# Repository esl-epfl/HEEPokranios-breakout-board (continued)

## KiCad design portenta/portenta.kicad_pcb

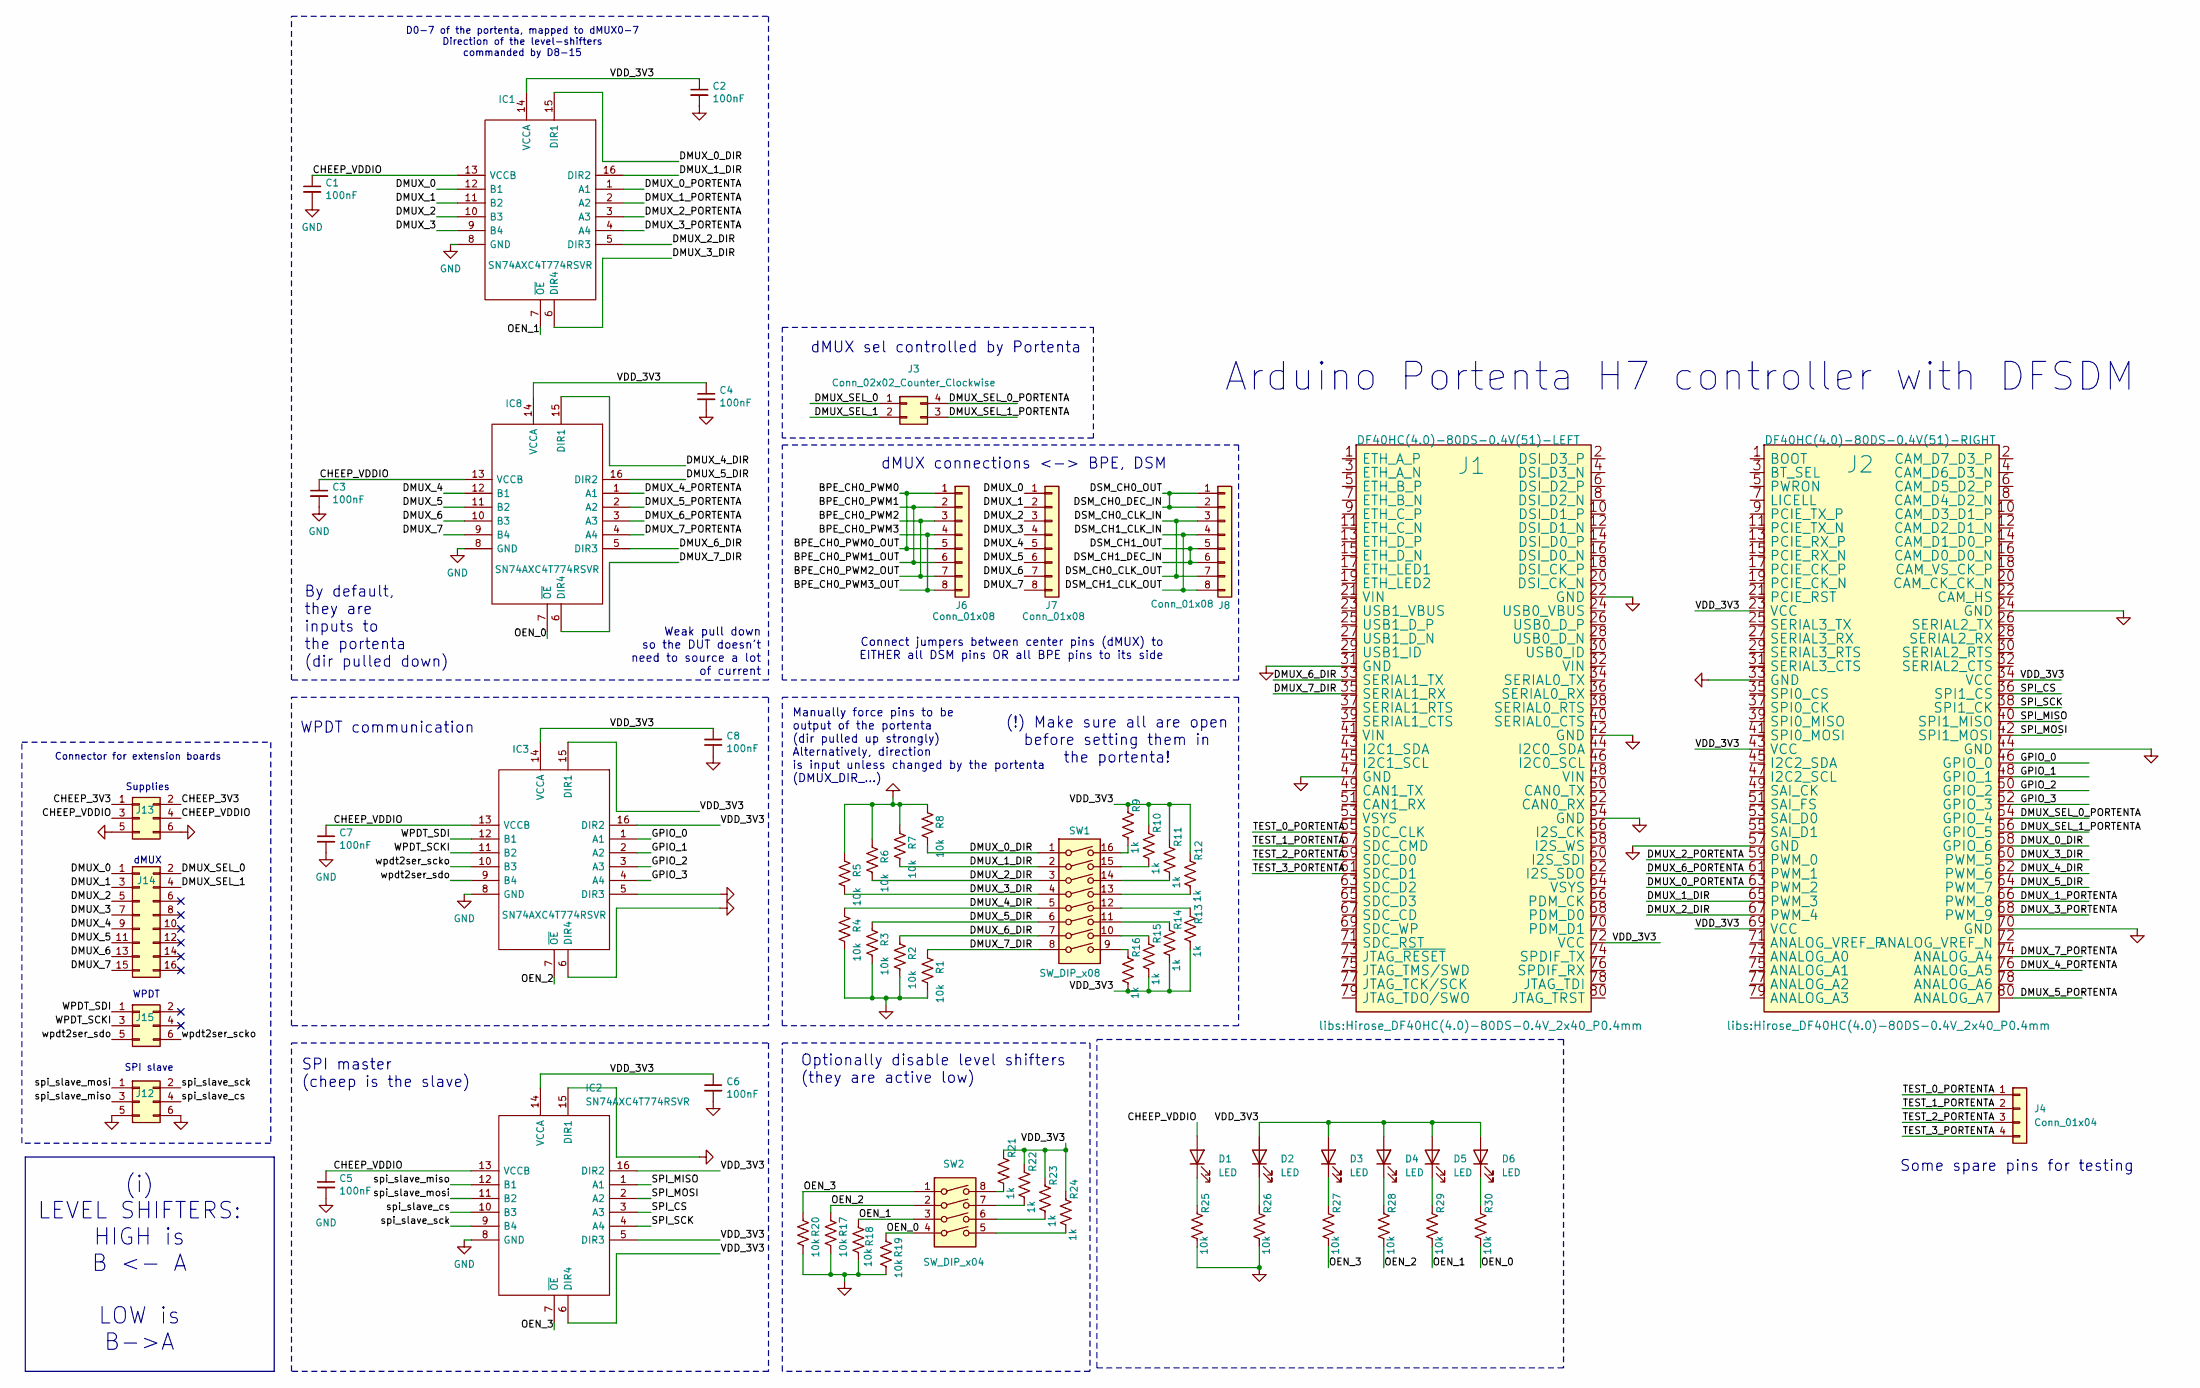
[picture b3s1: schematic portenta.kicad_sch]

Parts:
C1, C2, C3, C4, C5, C6, C7, C8: 100nF; C_0603_1608Metric; Mouser Part Number 80-C0805C104Z3V; Digikey Part Number 399-9158-1-ND
D1, D2, D3, D4, D5, D6: LED; LED_0603_1608Metric
IC1, IC2, IC3, IC8: SN74AXC4T774RSVR; TI-UQFN-16; Manufacturer_Part_Number SN74AXC4T774RSVR; Mouser Part Number 595-SN74AXC4T774RSVR
J1: DF40HC(4.0)-80DS-0.4V(51)-LEFT; Hirose_DF40HC(4.0)-80DS-0.4V_2x40_P0.4mm
J2: DF40HC(4.0)-80DS-0.4V(51)-RIGHT; Hirose_DF40HC(4.0)-80DS-0.4V_2x40_P0.4mm
J3: Conn_02x02_Counter_Clockwise; PinHeader_2x02_P2.54mm_Vertical
J4: Conn_01x04; PinHeader_1x04_P2.54mm_Vertical
J6, J7, J8: Conn_01x08; PinHeader_1x08_P2.54mm_Vertical
J12, J13, J15: Conn_02x03_Odd_Even; PinHeader_2x03_P2.54mm_Horizontal
J14: Conn_02x08_Odd_Even; PinHeader_2x08_P2.54mm_Horizontal
R1, R2, R3, R4, R5, R6, R7, R8, R17, R18, R19, R20, R25, R26, R27, R28, R29, R30: 10k; R_0603_1608Metric
R9, R10, R11, R12, R13, R14, R15, R16, R21, R22, R23, R24: 1k; R_0603_1608Metric
SW1: SW_DIP_x08; SW_DIP_SPSTx08_Slide_6.7x21.88mm_W8.61mm_P2.54mm_LowProfile
SW2: SW_DIP_x04; SW_DIP_SPSTx04_Slide_6.7x11.72mm_W8.61mm_P2.54mm_LowProfile

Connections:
/BPE_CH0_PWM0: J6.1, J6.5
/BPE_CH0_PWM1: J6.2, J6.6
/BPE_CH0_PWM2: J6.3, J6.7
/BPE_CH0_PWM3: J6.4, J6.8
/CHEEP_3V3: J13.1, J13.2
/CHEEP_VDDIO: C1.1, C3.1, C5.1, C7.1, D1.2 (A), IC1.13 (VCCB), IC2.13 (VCCB), IC3.13 (VCCB), IC8.13 (VCCB), J13.3, J13.4
/DMUX_0: IC1.12 (B1), J7.1, J14.1
/DMUX_0_DIR: IC1.15 (DIR1), J2.58 (GPIO_6), R8.2, SW1.1
/DMUX_0_PORTENTA: IC1.1 (A1), J2.63 (PWM_2)
/DMUX_1: IC1.11 (B2), J7.2, J14.3
/DMUX_1_DIR: IC1.16 (DIR2), J2.65 (PWM_3), R7.2, SW1.2
/DMUX_1_PORTENTA: IC1.2 (A2), J2.66 (PWM_8)
/DMUX_2: IC1.10 (B3), J7.3, J14.5
/DMUX_2_DIR: IC1.5 (DIR3), J2.67 (PWM_4), R6.2, SW1.3
/DMUX_2_PORTENTA: IC1.3 (A3), J2.59 (PWM_0)
/DMUX_3: IC1.9 (B4), J7.4, J14.7
/DMUX_3_DIR: IC1.6 (DIR4), J2.60 (PWM_5), R5.2, SW1.4
/DMUX_3_PORTENTA: IC1.4 (A4), J2.68 (PWM_9)
/DMUX_4: IC8.12 (B1), J7.5, J14.9
/DMUX_4_DIR: IC8.15 (DIR1), J2.62 (PWM_6), R4.1, SW1.5
/DMUX_4_PORTENTA: IC8.1 (A1), J2.76 (ANALOG_A5)
/DMUX_5: IC8.11 (B2), J7.6, J14.11
/DMUX_5_DIR: IC8.16 (DIR2), J2.64 (PWM_7), R3.1, SW1.6
/DMUX_5_PORTENTA: IC8.2 (A2), J2.80 (ANALOG_A7)
/DMUX_6: IC8.10 (B3), J7.7, J14.13
/DMUX_6_DIR: IC8.5 (DIR3), J1.33 (SERIAL1_TX), R2.1, SW1.7
/DMUX_6_PORTENTA: IC8.3 (A3), J2.61 (PWM_1)
/DMUX_7: IC8.9 (B4), J7.8, J14.15
/DMUX_7_DIR: IC8.6 (DIR4), J1.35 (SERIAL1_RX), R1.1, SW1.8
/DMUX_7_PORTENTA: IC8.4 (A4), J2.74 (ANALOG_A4)
/DMUX_SEL_0: J3.1, J14.2
/DMUX_SEL_0_PORTENTA: J2.54 (GPIO_4), J3.4
/DMUX_SEL_1: J3.2, J14.4
/DMUX_SEL_1_PORTENTA: J2.56 (GPIO_5), J3.3
/DSM_CH0_CLK_IN: J8.3, J8.7
/DSM_CH0_DEC_IN: J8.1, J8.2
/DSM_CH1_CLK_IN: J8.4, J8.8
/DSM_CH1_DEC_IN: J8.5, J8.6
/GPIO_0: IC3.1 (A1), J2.46 (GPIO_0)
/GPIO_1: IC3.2 (A2), J2.48 (GPIO_1)
/GPIO_2: IC3.3 (A3), J2.50 (GPIO_2)
/GPIO_3: IC3.4 (A4), J2.52 (GPIO_3)
/OEN_0: IC8.7 (~OE), R19.1, R30.2, SW2.4
/OEN_1: IC1.7 (~OE), R18.1, R29.2, SW2.3
/OEN_2: IC3.7 (~OE), R17.1, R28.2, SW2.2
/OEN_3: IC2.7 (~OE), R20.1, R27.2, SW2.1
/SPI_CS: IC2.3 (A3), J2.36 (SPI1_CS)
/SPI_MISO: IC2.1 (A1), J2.40 (SPI1_MISO)
/SPI_MOSI: IC2.2 (A2), J2.42 (SPI1_MOSI)
/SPI_SCK: IC2.4 (A4), J2.38 (SPI1_CK)
/TEST_0_PORTENTA: J1.55 (SDC_CLK), J4.1
/TEST_1_PORTENTA: J1.57 (SDC_CMD), J4.2
/TEST_2_PORTENTA: J1.59 (SDC_D0), J4.3
/TEST_3_PORTENTA: J1.61 (SDC_D1), J4.4
/VDD_3V3: C2.1, C4.1, C6.1, C8.1, D2.2 (A), D3.2 (A), D4.2 (A), D5.2 (A), D6.2 (A), IC1.14 (VCCA), IC2.5 (DIR3), IC2.6 (DIR4), IC2.14 (VCCA), IC2.16 (DIR2), IC3.14 (VCCA), IC3.15 (DIR1), IC3.16 (DIR2), IC8.14 (VCCA), J1.72 (VCC), J2.23 (VCC), J2.34 (VCC), J2.43 (VCC), J2.69 (VCC), R9.1, R10.1, R11.1, R12.1, R13.2, R14.2, R15.2, R16.2, R21.1, R22.1, R23.1, R24.1
/WPDT_SCKI: IC3.11 (B2), J15.3
/WPDT_SDI: IC3.12 (B1), J15.1
/spi_slave_cs: IC2.10 (B3), J12.4
/spi_slave_miso: IC2.12 (B1), J12.3
/spi_slave_mosi: IC2.11 (B2), J12.1
/spi_slave_sck: IC2.9 (B4), J12.2
/wpdt2ser_scko: IC3.10 (B3), J15.6
/wpdt2ser_sdo: IC3.9 (B4), J15.5
GND: C1.2, C2.2, C3.2, C4.2, C5.2, C6.2, C7.2, C8.2, IC1.8 (GND), IC2.8 (GND), IC2.15 (DIR1), IC3.5 (DIR3), IC3.6 (DIR4), IC3.8 (GND), IC8.8 (GND), J1.22 (GND), J1.31 (GND), J1.42 (GND), J1.47 (GND), J1.54 (GND), J2.24 (GND), J2.33 (GND), J2.44 (GND), J2.57 (GND), J2.70 (GND), J12.5, J12.6, J13.5, J13.6, R1.2, R2.2, R3.2, R4.2, R5.1, R6.1, R7.1, R8.1, R17.2, R18.2, R19.2, R20.2, R25.2, R26.2
unnamed: D1.1 (K), R25.1
unnamed: D2.1 (K), R26.1
unnamed: D3.1 (K), R27.1
unnamed: D4.1 (K), R28.1
unnamed: D5.1 (K), R29.1
unnamed: D6.1 (K), R30.1
unnamed: R9.2, SW1.16
unnamed: R10.2, SW1.15
unnamed: R11.2, SW1.14
unnamed: R12.2, SW1.13
unnamed: R13.1, SW1.12
unnamed: R14.1, SW1.11
unnamed: R15.1, SW1.10
unnamed: R16.1, SW1.9
unnamed: R21.2, SW2.8
unnamed: R22.2, SW2.7
unnamed: R23.2, SW2.6
unnamed: R24.2, SW2.5

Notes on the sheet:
Some spare pins for testing
Connect jumpers between center pins (dMUX) to EITHER all DSM pins OR all BPE pins to its side
(i) LEVEL SHIFTERS: HIGH is B <- A LOW is B->A
Weak pull down so the DUT doesn't need to source a lot of current
Arduino Portenta H7 controller with DFSDM
Optionally disable level shifters (they are active low)
WPDT
SPI slave
Manually force pins to be output of the portenta (dir pulled up strongly) Alternatively, direction is input unless changed by the portenta (DMUX_DIR_...)
dMUX connections <-> BPE, DSM
WPDT communication
dMUX
SPI master (cheep is the slave)
Supplies
D0-7 of the portenta, mapped to dMUX0-7 Direction of the level-shifters commanded by D8-15
Connector for extension boards
By default, they are inputs to the portenta (dir pulled down)
(!) Make sure all are open before setting them in the portenta!
dMUX sel controlled by Portenta

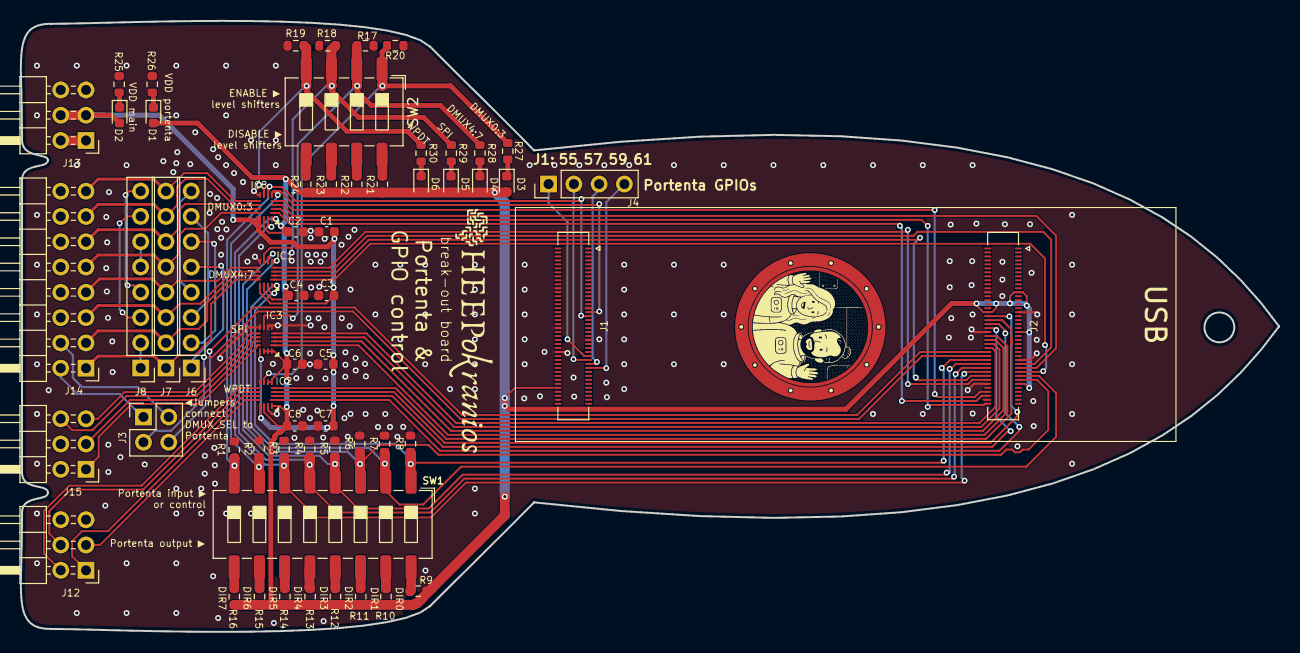
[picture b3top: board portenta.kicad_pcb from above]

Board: 2 copper layers, 126.4 x 61.4 mm, 61 parts (0 on the bottom side), 82 nets.

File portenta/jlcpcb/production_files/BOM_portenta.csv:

Comment,Designator,Footprint,LCSC,Qty
100n,"C1,C2,C3,C4,C5,C6,C7,C8",C_0603_1608Metric,C30926,8
LED,"D1,D2,D3,D4,D5,D6",LED_0603_1608Metric,C84263,6
SN74AXC4T774RSVR,"IC1,IC2,IC3,IC8",TI-UQFN-16,C1849454,4
DF40HC(4.0)-80DS-0.4V(51),"J1,J2",Hirose_DF40HC(4.0)-80DS-0.4V_2x40_P0.4mm,C5254351,2
Conn_02x02_Counter_Clockwise,J3,PinHeader_2x02_P2.54mm_Vertical,C66690,1
Conn_01x04,J4,PinHeader_1x04_P2.54mm_Vertical,C52016392,1
Conn_01x08,"J6,J7,J8",PinHeader_1x08_P2.54mm_Vertical,C32713274,3
Conn_02x03_Odd_Even,"J12,J13,J15",PinHeader_2x03_P2.54mm_Horizontal,C41417351,3
Conn_02x08_Odd_Even,J14,PinHeader_2x08_P2.54mm_Horizontal,C41417356,1
10k,"R1,R2,R3,R4,R5,R6,R7,R8,R17,R18,R19,R20,R25,R26,R27,R28,R29,R30",R_0603_1608Metric,C2930027,18
1k,"R9,R10,R11,R12,R13,R14,R15,R16,R21,R22,R23,R24",R_0603_1608Metric,C110776,12
SW_DIP_x08,SW1,SW_DIP_SPSTx08_Slide_6.7x21.88mm_W8.61mm_P2.54mm_LowProfile,C5439767,1
SW_DIP_x04,SW2,SW_DIP_SPSTx04_Slide_6.7x11.72mm_W8.61mm_P2.54mm_LowProfile,C5439763,1

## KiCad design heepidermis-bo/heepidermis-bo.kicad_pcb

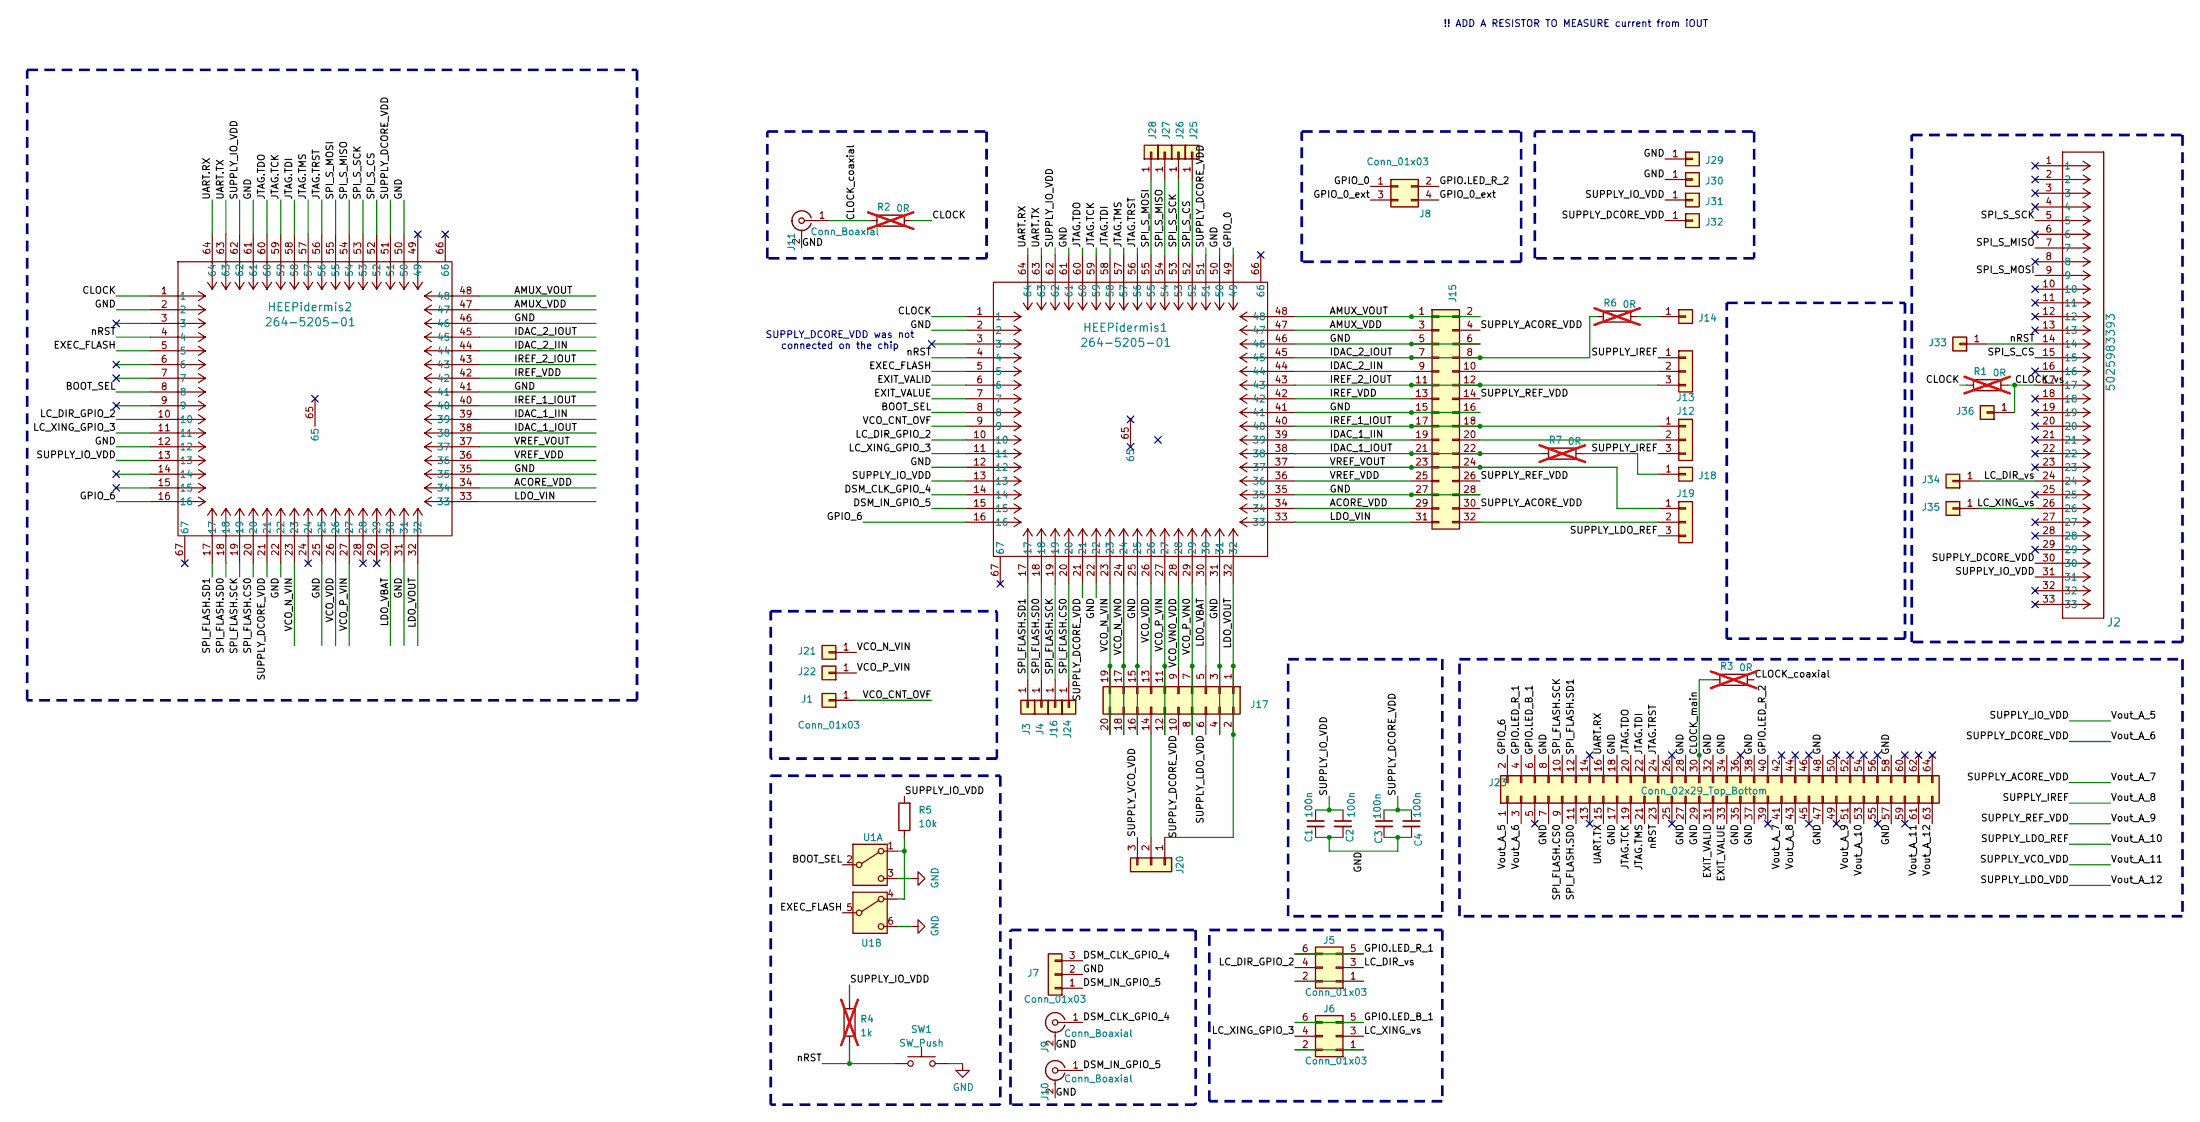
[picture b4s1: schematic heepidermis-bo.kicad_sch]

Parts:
C1, C2, C3, C4: 100n; C_0603_1608Metric; Mouser Part Number 80-C0805C104Z3V; Digikey Part Number 399-9158-1-ND
HEEPidermis1: 264-5205-01; CONN_5205_3MM
HEEPidermis2: 264-5205-01; QFN-64-1EP_9x9mm_P0.5mm_EP3.4x3.4mm
J1, J14, J18, J21, J22: Conn_01x03; PinHeader_1x01_P1.27mm_Vertical
J2: 5025983393; CONN_502598-3393_MOL
J3, J4, J16, J24, J25, J26, J27, J28, J29, J30, J31, J32, J33, J34, J35, J36: Conn_01x03; TestPoint_THTPad_1.0x1.0mm_Drill0.5mm
J5, J6: Conn_01x03; PinHeader_2x03_P1.27mm_Vertical
J7, J12, J13, J19, J20: Conn_01x03; PinHeader_1x03_P2.54mm_Vertical
J8: Conn_01x03; PinHeader_2x02_P1.27mm_Vertical
J9, J10, J11: Conn_Boaxial; SMA_Amphenol_901-144_Vertical
J15: Conn_02x16_Odd_Even; PinHeader_02x16_P2.54mm_Vertical
J17: Conn_02x10_Odd_Even; PinHeader_2x10_P2.54mm_Vertical
J23: Conn_02x29_Top_Bottom; PinHeader_2x32_P2.54mm_Vertical
R1, R2, R3: 0R; R0402; not fitted
R4: 1k; R_0603_1608Metric; LCSC C21190; not fitted
R5: 10k; R_0603_1608Metric; LCSC C21190
R6, R7: 0R; R_0402_1005Metric; not fitted
SW1: SW_Push; SW_Push_1P1T_NO_CK_KMR2
U1: SPDT-2pos-CAS-D20B1

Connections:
/ACORE_VDD: HEEPidermis1.34, HEEPidermis2.34, J15.29
/AMUX_VDD: HEEPidermis1.47, HEEPidermis2.47, J15.3
/AMUX_VOUT: HEEPidermis1.48, HEEPidermis2.48, J15.1, J15.2
/BOOT_SEL: HEEPidermis1.8, HEEPidermis2.8, U1.2 (B)
/CLOCK: HEEPidermis1.1, HEEPidermis2.1, R1.1, R2.2
/CLOCK_coaxial: J11.1 (In), R2.1, R3.2
/CLOCK_main: J23.30, R3.1
/CLOCK_vs: J2.17, J36.1, R1.2
/DSM_CLK_GPIO_4: HEEPidermis1.14, J7.3, J9.1 (In)
/DSM_IN_GPIO_5: HEEPidermis1.15, J7.1, J10.1 (In)
/EXEC_FLASH: HEEPidermis1.5, HEEPidermis2.5, U1.5 (B)
/EXIT_VALID: HEEPidermis1.6, J23.31
/EXIT_VALUE: HEEPidermis1.7, J23.33
/GPIO.LED_B_1: J6.5, J6.6, J23.6
/GPIO.LED_R_1: J5.5, J5.6, J23.4
/GPIO.LED_R_2: J8.2, J23.40
/GPIO_0: HEEPidermis1.49, J8.1
/GPIO_0_ext: J8.3, J8.4
/GPIO_6: HEEPidermis1.16, HEEPidermis2.16, J23.2
/IDAC_1_IIN: HEEPidermis1.39, HEEPidermis2.39, J15.19
/IDAC_1_IOUT: HEEPidermis1.38, HEEPidermis2.38, J15.21, J15.22, R7.1
/IDAC_2_IIN: HEEPidermis1.44, HEEPidermis2.44, J15.9
/IDAC_2_IOUT: HEEPidermis1.45, HEEPidermis2.45, J15.7, J15.8, R6.1
/IREF_1_IOUT: HEEPidermis1.40, HEEPidermis2.40, J12.1, J15.17, J15.18
/IREF_2_IOUT: HEEPidermis1.43, HEEPidermis2.43, J13.3, J15.11, J15.12
/IREF_VDD: HEEPidermis1.42, HEEPidermis2.42, J15.13
/JTAG.TCK: HEEPidermis1.59, HEEPidermis2.59, J23.19
/JTAG.TDI: HEEPidermis1.58, HEEPidermis2.58, J23.22
/JTAG.TDO: HEEPidermis1.60, HEEPidermis2.60, J23.20
/JTAG.TMS: HEEPidermis1.57, HEEPidermis2.57, J23.21
/JTAG.TRST: HEEPidermis1.56, HEEPidermis2.56, J23.24
/LC_DIR_GPIO_2: HEEPidermis1.10, HEEPidermis2.10, J5.4
/LC_DIR_vs: J2.24, J5.3, J34.1
/LC_XING_GPIO_3: HEEPidermis1.11, HEEPidermis2.11, J6.4
/LC_XING_vs: J2.26, J6.3, J35.1
/LDO_VBAT: HEEPidermis1.30, HEEPidermis2.30, J17.5
/LDO_VIN: HEEPidermis1.33, HEEPidermis2.33, J15.31
/LDO_VOUT: HEEPidermis1.32, HEEPidermis2.32, J17.1, J17.2, J20.1
/SPI_FLASH.CS0: HEEPidermis1.20, HEEPidermis2.20, J23.9, J24.1
/SPI_FLASH.SCK: HEEPidermis1.19, HEEPidermis2.19, J16.1, J23.10
/SPI_FLASH.SD0: HEEPidermis1.18, HEEPidermis2.18, J4.1, J23.11
/SPI_FLASH.SD1: HEEPidermis1.17, HEEPidermis2.17, J3.1, J23.12
/SPI_S_CS: HEEPidermis1.52, HEEPidermis2.52, J2.15, J25.1
/SPI_S_MISO: HEEPidermis1.54, HEEPidermis2.54, J2.7, J27.1
/SPI_S_MOSI: HEEPidermis1.55, HEEPidermis2.55, J2.9, J28.1
/SPI_S_SCK: HEEPidermis1.53, HEEPidermis2.53, J2.5, J26.1
/SUPPLY_ACORE_VDD: J15.4, J15.30, J23.41
/SUPPLY_DCORE_VDD: C3.1, C4.1, HEEPidermis1.21, HEEPidermis1.51, HEEPidermis2.21, HEEPidermis2.51, J2.30, J17.10, J23.3, J32.1
/SUPPLY_IO_VDD: C1.1, C2.1, HEEPidermis1.13, HEEPidermis1.62, HEEPidermis2.13, HEEPidermis2.62, J2.31, J23.1, J31.1, R4.2, R5.2
/SUPPLY_IREF: J12.3, J13.1, J23.43
/SUPPLY_LDO_REF: J19.3, J23.53
/SUPPLY_LDO_VDD: J17.6, J23.63
/SUPPLY_REF_VDD: J15.14, J15.26, J23.51
/SUPPLY_VCO_VDD: J20.3, J23.61
/UART.RX: HEEPidermis1.64, HEEPidermis2.64, J23.16
/UART.TX: HEEPidermis1.63, HEEPidermis2.63, J23.15
/VCO_CNT_OVF: HEEPidermis1.9, J1.1
/VCO_N_VIN: HEEPidermis1.23, HEEPidermis2.23, J17.19, J17.20, J21.1
/VCO_N_VN0: HEEPidermis1.24, J17.17, J17.18
/VCO_P_VIN: HEEPidermis1.27, HEEPidermis2.27, J17.11, J17.12, J22.1
/VCO_P_VN0: HEEPidermis1.29, J17.7, J17.8
/VCO_VDD: HEEPidermis1.26, HEEPidermis2.26, J17.13
/VCO_VN0_VDD: HEEPidermis1.28, J17.9
/VREF_VDD: HEEPidermis1.36, HEEPidermis2.36, J15.25
/VREF_VOUT: HEEPidermis1.37, HEEPidermis2.37, J15.23, J15.24, J19.1
/nRST: HEEPidermis1.4, HEEPidermis2.4, J2.14, J23.23, J33.1, R4.1, SW1.1
GND: C1.2, C2.2, C3.2, C4.2, HEEPidermis1.2, HEEPidermis1.12, HEEPidermis1.22, HEEPidermis1.25, HEEPidermis1.31, HEEPidermis1.35, HEEPidermis1.41, HEEPidermis1.46, HEEPidermis1.50, HEEPidermis1.61, HEEPidermis2.2, HEEPidermis2.12, HEEPidermis2.22, HEEPidermis2.25, HEEPidermis2.31, HEEPidermis2.35, HEEPidermis2.41, HEEPidermis2.46, HEEPidermis2.50, HEEPidermis2.61, J7.2, J9.2 (Ext), J10.2 (Ext), J11.2 (Ext), J15.5, J15.6, J15.15, J15.16, J15.27, J15.28, J17.3, J17.4, J17.15, J17.16, J23.7, J23.8, J23.17, J23.18, J23.27, J23.28, J23.29, J23.32, J23.34, J23.35, J23.37, J23.38, J23.47, J23.48, J23.57, J23.58, J29.1, J30.1, SW1.2, U1.3 (C), U1.6 (C)
unnamed: J5.1, J5.2
unnamed: J6.1, J6.2
unnamed: J12.2, J15.20
unnamed: J13.2, J15.10
unnamed: J14.1, R6.2
unnamed: J15.32, J19.2
unnamed: J17.14, J20.2
unnamed: J18.1, R7.2
unnamed: R5.1, U1.1 (A), U1.4 (A)

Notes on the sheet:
SUPPLY_DCORE_VDD was not connected on the chip
!! ADD A RESISTOR TO MEASURE current from iOUT

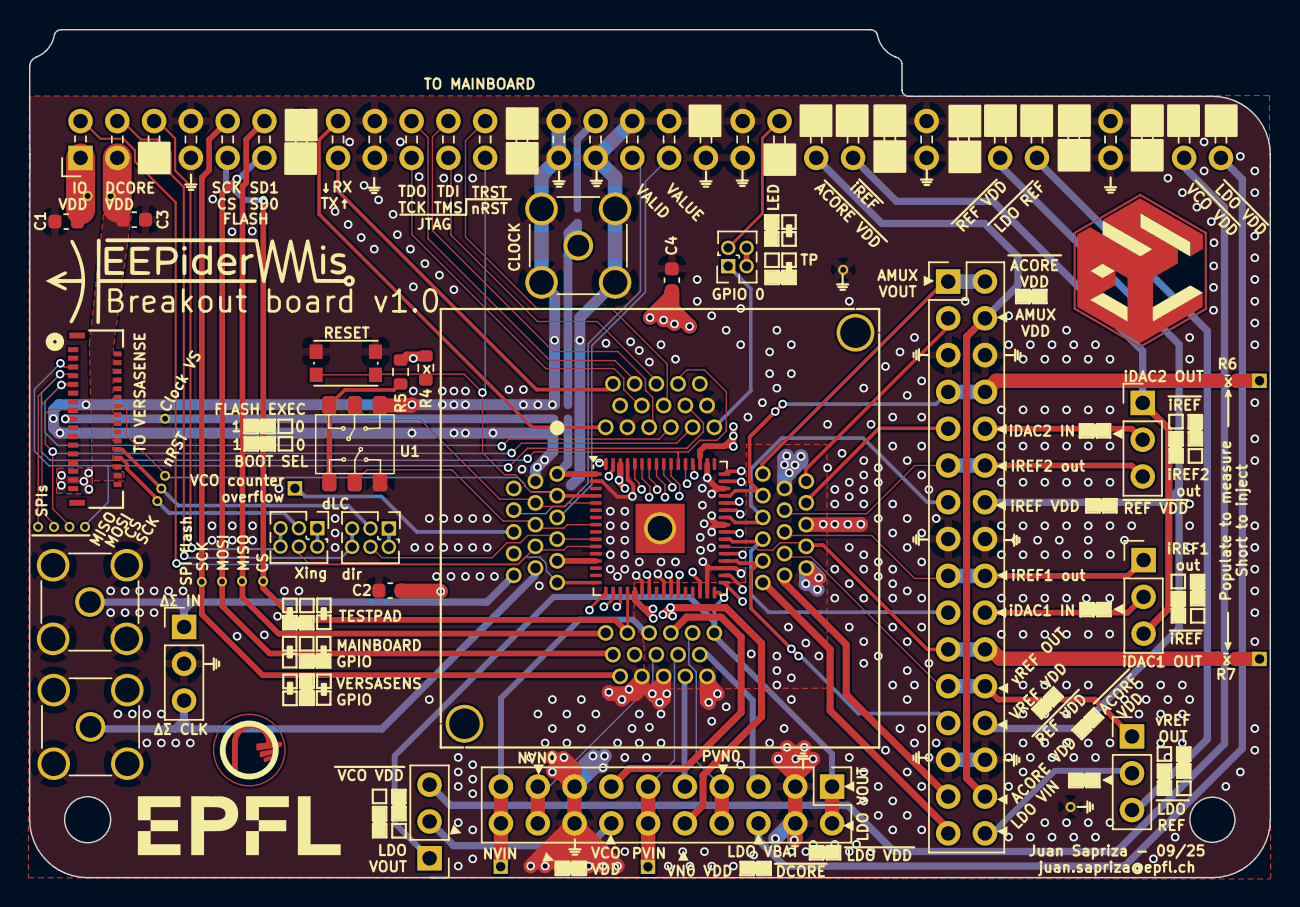
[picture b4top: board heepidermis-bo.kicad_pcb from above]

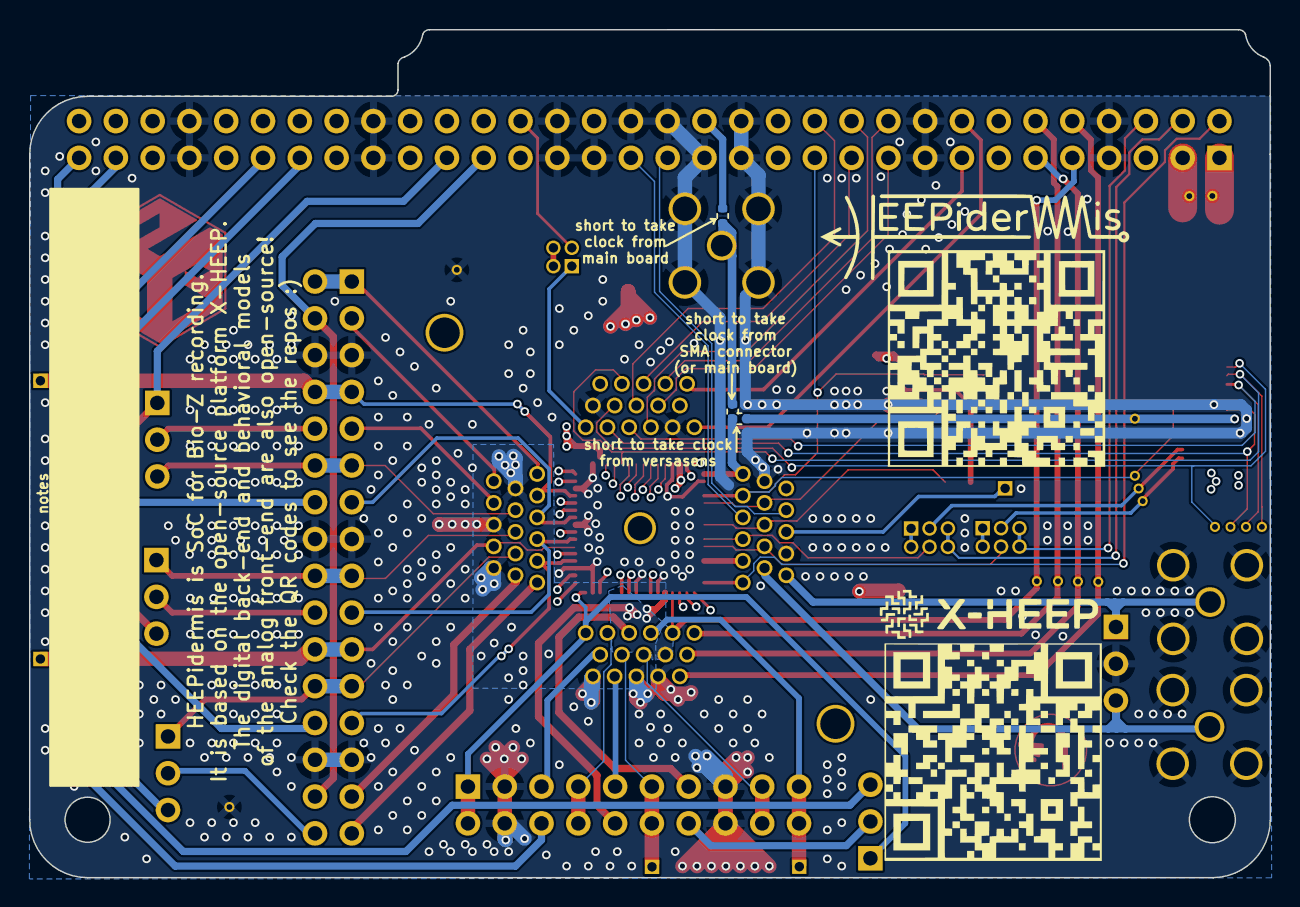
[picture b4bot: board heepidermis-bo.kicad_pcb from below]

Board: 4 copper layers, 85.7 x 58.5 mm, 51 parts (3 on the bottom side), 76 nets.

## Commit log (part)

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2025-09-27 Previous to changing connector to 2.54
2025-09-27 Finished adding the large connector. Missing gpios and qfn footprint
2025-09-30 Almost done adding footprint of qfn64
2025-10-01 DRC clean
2025-10-01 Uploaded gerbers
2025-10-03 Added zskin
2025-11-18 Cleander repo
2025-11-18 Added diagram
